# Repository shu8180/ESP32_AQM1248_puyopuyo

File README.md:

# ESP32_AQM1248_puyopuyo
ESP32とLCDディスプレイのAQM1248を使用してぷよぷよを作成

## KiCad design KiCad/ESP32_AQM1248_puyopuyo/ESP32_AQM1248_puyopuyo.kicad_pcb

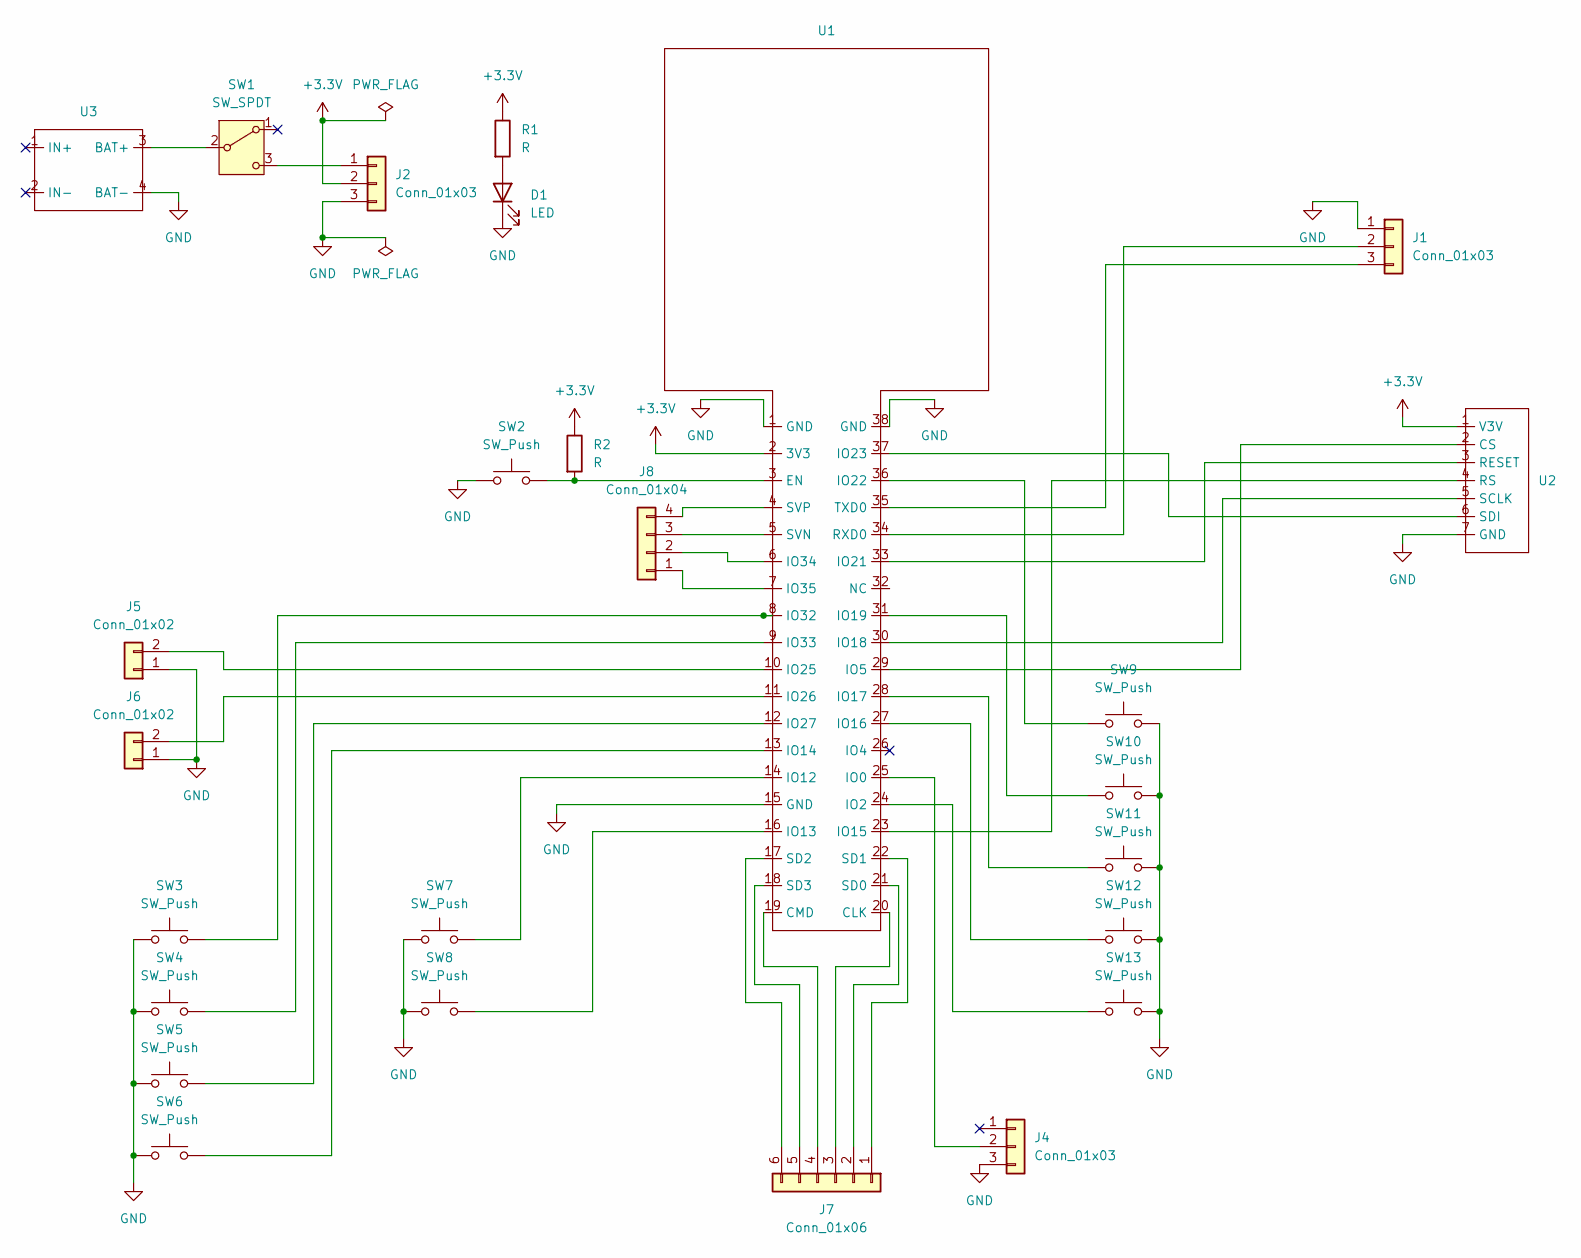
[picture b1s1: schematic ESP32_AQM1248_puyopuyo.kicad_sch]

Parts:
D1: LED; LED_D3.0mm
J1, J2, J4: Conn_01x03; PinHeader_1x03_P2.54mm_Vertical
J5, J6: Conn_01x02; PinHeader_1x02_P2.54mm_Vertical
J7: Conn_01x06; PinHeader_1x06_P2.54mm_Vertical
J8: Conn_01x04; PinHeader_1x04_P2.54mm_Vertical
R1, R2: R; R_Axial_DIN0411_L9.9mm_D3.6mm_P12.70mm_Horizontal
SW1: SW_SPDT; SW_Slide_1P2T_CK_OS102011MS2Q
SW2, SW3, SW4, SW5, SW6, SW7, SW8, SW9, SW10, SW11, SW12, SW13: SW_Push; SW_PUSH_6mm
U1: ESP32-AKITUKI
U2: AQM1248A-LCD
U3: BAT-MNG

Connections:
+3.3V: J2.2, R1.1, R2.1, U1.2 (3V3), U2.1 (V3V)
GND: D1.1 (K), J1.1, J2.3, J4.3, J5.1, J6.1, SW2.1, SW3.1, SW4.1, SW5.1, SW6.1, SW7.1, SW8.1, SW9.2, SW10.2, SW11.2, SW12.2, SW13.2, U1.1 (GND), U1.15 (GND), U1.38 (GND), U2.7 (GND), U3.4 (BAT-)
unnamed: D1.2 (A), R1.2
unnamed: J1.2, U1.34 (RXD0)
unnamed: J1.3, U1.35 (TXD0)
unnamed: J2.1, SW1.3 (C)
unnamed: J4.2, U1.25 (IO0)
unnamed: J5.2, U1.10 (IO25)
unnamed: J6.2, U1.11 (IO26)
unnamed: J7.1, U1.22 (SD1)
unnamed: J7.2, U1.21 (SD0)
unnamed: J7.3, U1.20 (CLK)
unnamed: J7.4, U1.19 (CMD)
unnamed: J7.5, U1.18 (SD3)
unnamed: J7.6, U1.17 (SD2)
unnamed: J8.1, U1.7 (IO35)
unnamed: J8.2, U1.6 (IO34)
unnamed: J8.3, U1.5 (SVN)
unnamed: J8.4, U1.4 (SVP)
unnamed: SW1.2 (B), U3.3 (BAT+)
unnamed: R2.2, SW2.2, U1.3 (EN)
unnamed: SW13.1, U1.24 (IO2)
unnamed: U1.29 (IO5), U2.2 (CS)
unnamed: SW7.2, U1.14 (IO12)
unnamed: SW8.2, U1.16 (IO13)
unnamed: SW6.2, U1.13 (IO14)
unnamed: U1.23 (IO15), U2.4 (RS)
unnamed: SW12.1, U1.27 (IO16)
unnamed: SW11.1, U1.28 (IO17)
unnamed: U1.30 (IO18), U2.5 (SCLK)
unnamed: SW10.1, U1.31 (IO19)
unnamed: U1.33 (IO21), U2.3 (RESET)
unnamed: SW9.1, U1.36 (IO22)
unnamed: U1.37 (IO23), U2.6 (SDI)
unnamed: SW5.2, U1.12 (IO27)
unnamed: SW3.2, U1.8 (IO32)
unnamed: SW4.2, U1.9 (IO33)

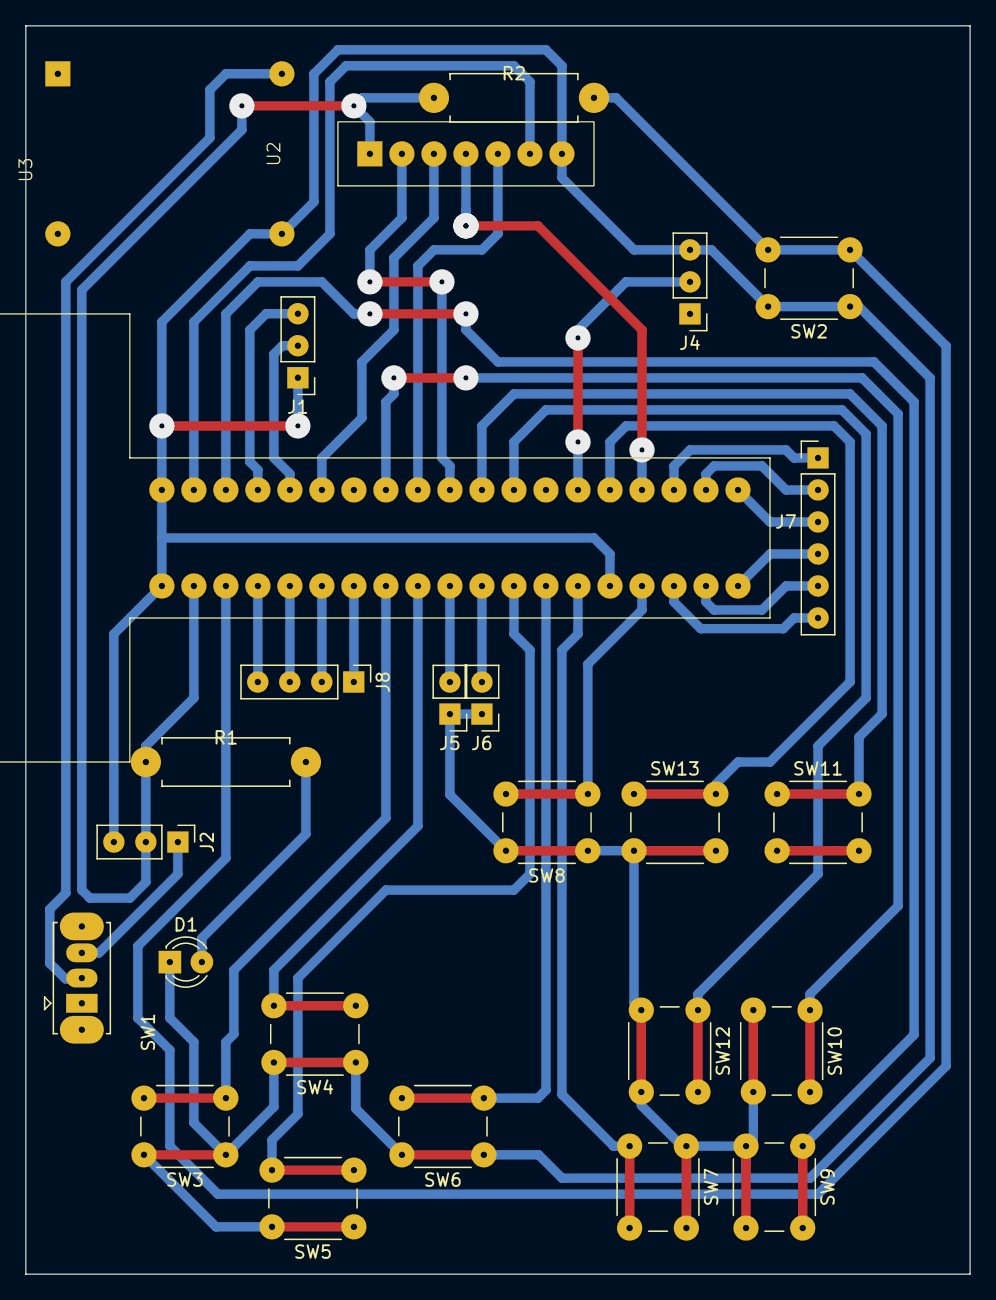
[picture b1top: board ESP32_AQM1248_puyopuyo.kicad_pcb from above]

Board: 2 copper layers, 74.9 x 99.1 mm, 26 parts (0 on the bottom side), 37 nets.

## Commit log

2024-01-14 UPpload ESP32 Program
2024-01-14 UPload KiCad data
2024-01-14 UPload 回路図とPCB
